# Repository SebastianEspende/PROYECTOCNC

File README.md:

# TALADRO CNC
### Introduccion

Este proyecto fue pensado y realizado con el fin de diseñar y construir un enrutador CNC de bajo costo, su 
principal función es agujerear placas PCB de producción caseras por estudiantes. Con este dispositivo se 
busca facilitar el proceso de la creación de proyectos que requieran placas electrónicas, permitiendo al 
usuario una mayor precisión y eficiencia en la perforación de placas, en comparación con los métodos 
manuales. Este proyecto también tiene como objetivo fomentar el aprendizaje practico de tecnologías CNC, 
de la electrónica y programación, con el fin de que sea una herramienta útil para los proyectos de electrónica 
y robótica.

#### Repositorio
- En el mismo se encuentran todos los recursos utilizados, como la parte electronica: donde se incluyen los diagramas y circuitos; los diseños 3D de las piezas utilizadas; y el codigo de programacion.
- No se incluyen las librerias, estas estaran al final de este archivo, algunas solo el nombre y otras en enlace a la pagina de donde provienen.

## Software

Se utiliza GRBL 1.1h, se incluye su link en el apartado de librerias

El codigo del ESP32 esta incluido por completo en este repositorio

## Para el futuro
A aquellos que les toque continuar nuestro proyecto, nos gustaria saberlo, les dejamos nuestros mails para que puedan contarnos, o si tienen alguna pregunta:
- espendesebastian@gmail.com
- josemcoronado671@gmail.com

### Palabras de precaución
los pines no son aleatorios, es importante que si quieren cambiarlo tengan en cuenta los grupos o puertos de los pines de un Arduino, si entran al cpu_map de GRBL se daran cuenta de lineas como esta para los 
pines que tienen algo en común como step de cada motor, dir de cada motor, limit switches, etc; 

```javascript
#define STEP_DDR        DDRD
#define STEP_PORT       PORTD
```
DDRD y PORTD no son solo nombres, se refieren al grupo de pines utiliado por los STEP en este caso, otro ejemplo
```javascript
#define DIRECTION_DDR     DDRD
#define DIRECTION_PORT    PORTD
```
Ambos utilizan el grupo D, que son del pin 0 al 7.
Grupo B utiliza pin 8 al 13.
es por eso que la declaracion de pines pareciera incorrecta, ejemplo 
#define X_LIMIT_BIT      1
Que utiliza el pin 9 pero se declara como 1, esto se debe a que utiliza el grupo B.

Para que la comunicacion entre el ESP32 y el Arduino funcione, tienen que tener el mismo GND, o al menos, conectarlos

### Librerias

- https://lcdmenu.forntoh.dev/overview/getting-started.html#installation
- https://github.com/gnea/grbl/releases/tag/v1.1h.20190825

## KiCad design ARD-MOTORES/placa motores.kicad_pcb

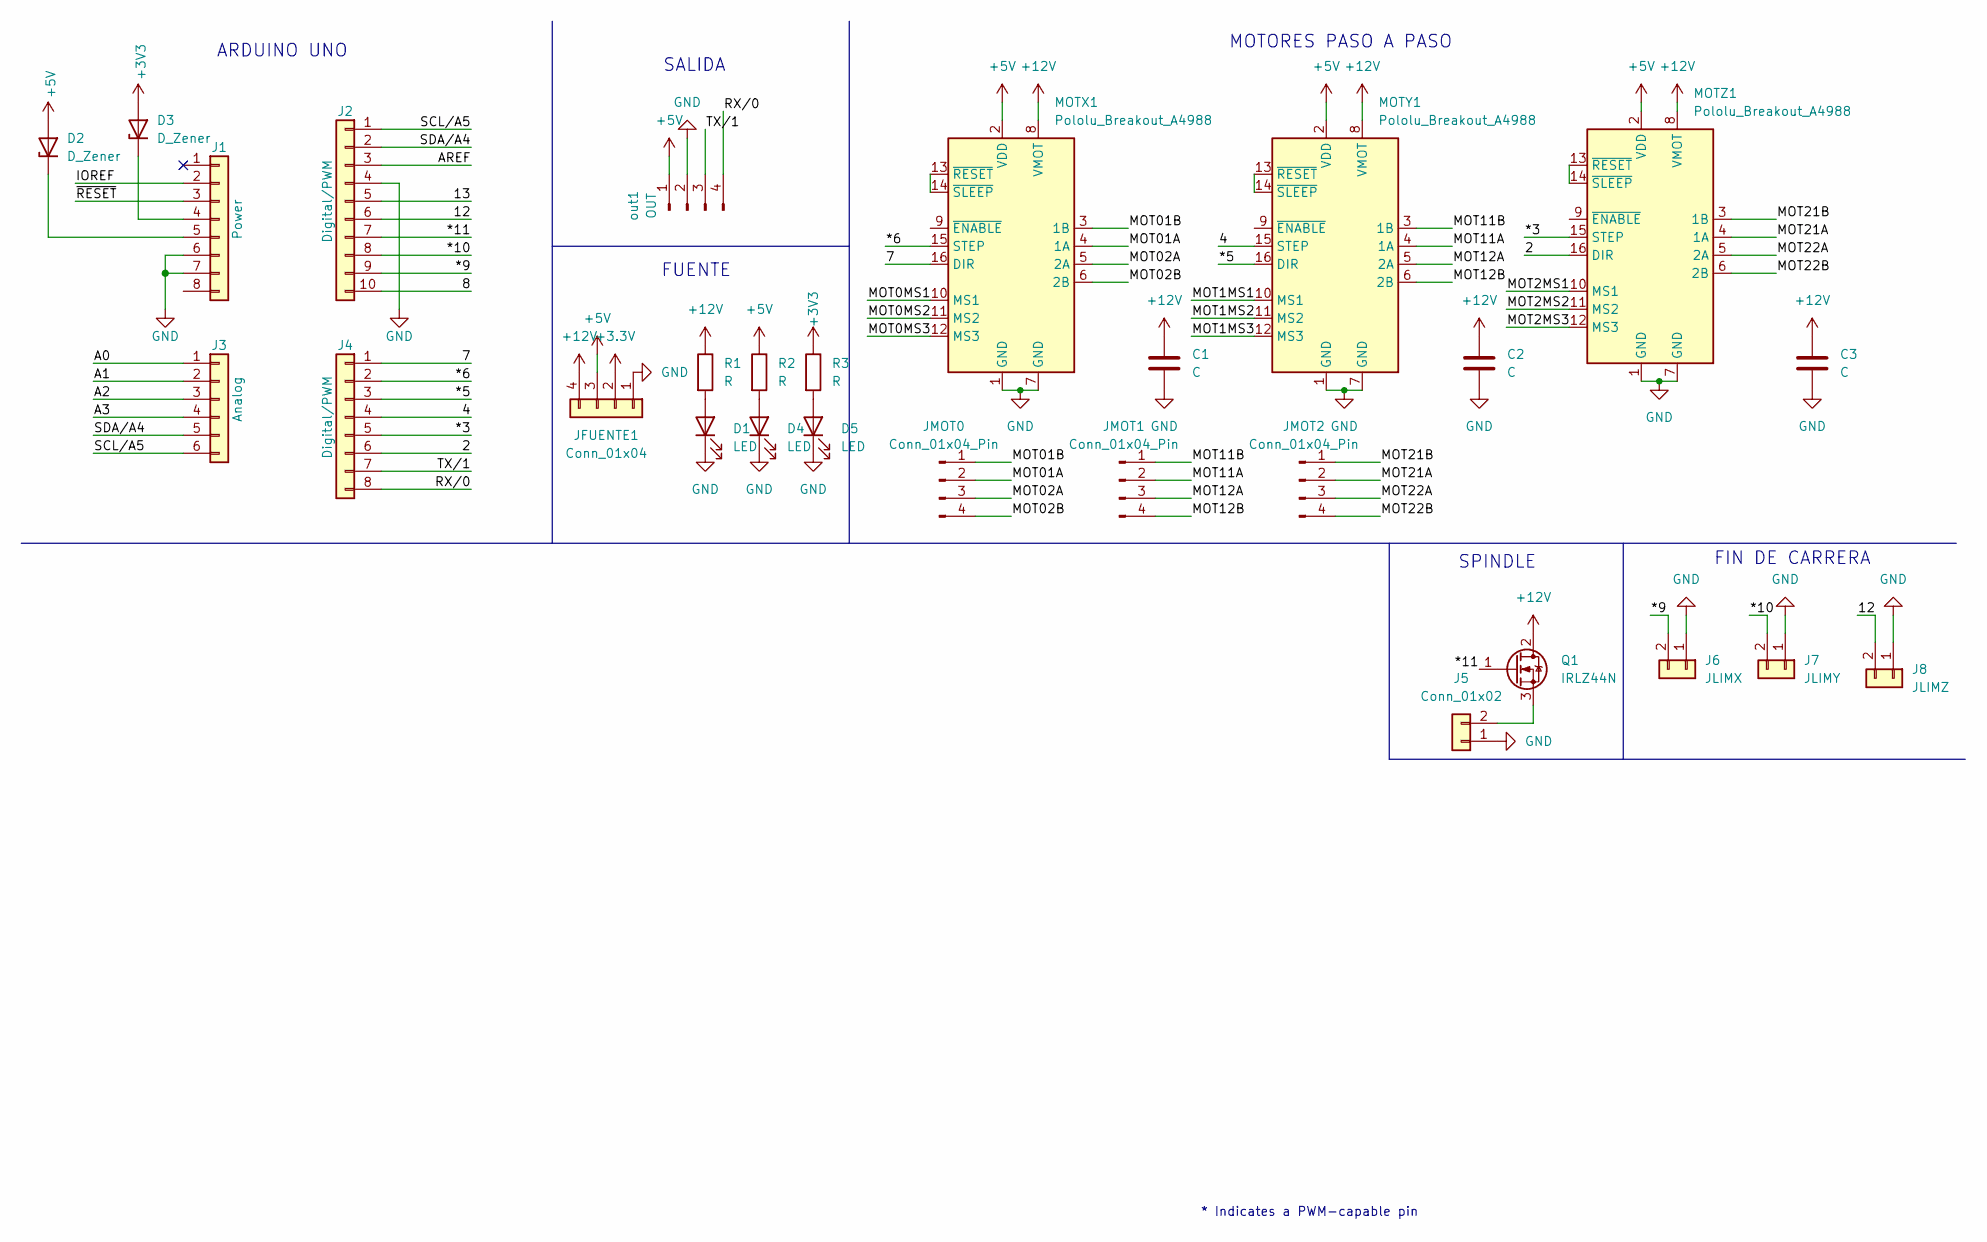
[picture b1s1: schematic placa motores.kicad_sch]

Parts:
C1, C2, C3: C; CP_Radial_D6.3mm_P2.50mm
D1, D4, D5: LED; LED_D5.0mm
D2, D3: D_Zener; D_DO-15_P12.70mm_Horizontal
J1: Power; PinSocket_1x08_P2.54mm_Vertical
J2: Digital/PWM; PinSocket_1x10_P2.54mm_Vertical
J3: Analog; PinSocket_1x06_P2.54mm_Vertical
J4: Digital/PWM; PinSocket_1x08_P2.54mm_Vertical
J5: Conn_01x02; PinHeader_1x02_P2.54mm_Vertical
J6: JLIMX; PinHeader_1x02_P2.54mm_Vertical
J7: JLIMY; PinHeader_1x02_P2.54mm_Vertical
J8: JLIMZ; PinHeader_1x02_P2.54mm_Vertical
JFUENTE1: Conn_01x04; TerminalBlock_Phoenix_MKDS-1,5-4_1x04_P5.00mm_Horizontal
JMOT0, JMOT1, JMOT2: Conn_01x04_Pin; PinHeader_1x04_P2.54mm_Vertical
MOTX1: Pololu_Breakout_A4988; Pololu_Breakout-16_15.2x20.3mm
MOTY1: Pololu_Breakout_A4988; Pololu_Breakout-16_15.2x20.3mm
MOTZ1: Pololu_Breakout_A4988; Pololu_Breakout-16_15.2x20.3mm
Q1: IRLZ44N; TO-220-3_Vertical
R1, R2, R3: R; R_Axial_DIN0414_L11.9mm_D4.5mm_P15.24mm_Horizontal
out1: OUT; PinHeader_1x04_P2.54mm_Vertical

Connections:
+5V: D2.2 (A), JFUENTE1.3, MOTX1.2 (VDD), MOTY1.2 (VDD), MOTZ1.2 (VDD), R2.1, out1.1
+12V: C1.1, C2.1, C3.1, JFUENTE1.4, MOTX1.8 (VMOT), MOTY1.8 (VMOT), MOTZ1.8 (VMOT), Q1.2 (D), R1.1
/2: J4.6, MOTZ1.16 (DIR)
/4: J4.4, MOTY1.15 (STEP)
/7: J4.1, MOTX1.16 (DIR)
/8: J2.10
/12: J2.6, J8.2
/13: J2.5
/*3: J4.5, MOTZ1.15 (STEP)
/*5: J4.3, MOTY1.16 (DIR)
/*6: J4.2, MOTX1.15 (STEP)
/*9: J2.9, J6.2
/*10: J2.8, J7.2
/*11: J2.7, Q1.1 (G)
/A0: J3.1
/A1: J3.2
/A2: J3.3
/A3: J3.4
/AREF: J2.3
/IOREF: J1.2
/MOT0MS1: MOTX1.10 (MS1)
/MOT0MS2: MOTX1.11 (MS2)
/MOT0MS3: MOTX1.12 (MS3)
/MOT01A: JMOT0.2, MOTX1.4 (1A)
/MOT01B: JMOT0.1, MOTX1.3 (1B)
/MOT1MS1: MOTY1.10 (MS1)
/MOT1MS2: MOTY1.11 (MS2)
/MOT1MS3: MOTY1.12 (MS3)
/MOT02A: JMOT0.3, MOTX1.5 (2A)
/MOT02B: JMOT0.4, MOTX1.6 (2B)
/MOT2MS1: MOTZ1.10 (MS1)
/MOT2MS2: MOTZ1.11 (MS2)
/MOT2MS3: MOTZ1.12 (MS3)
/MOT11A: JMOT1.2, MOTY1.4 (1A)
/MOT11B: JMOT1.1, MOTY1.3 (1B)
/MOT12A: JMOT1.3, MOTY1.5 (2A)
/MOT12B: JMOT1.4, MOTY1.6 (2B)
/MOT21A: JMOT2.2, MOTZ1.4 (1A)
/MOT21B: JMOT2.1, MOTZ1.3 (1B)
/MOT22A: JMOT2.3, MOTZ1.5 (2A)
/MOT22B: JMOT2.4, MOTZ1.6 (2B)
/RX/0: J4.8, out1.4
/SCL/A5: J2.1, J3.6
/SDA/A4: J2.2, J3.5
/TX/1: J4.7, out1.3
/~RESET: J1.3
GND: C1.2, C2.2, C3.2, D1.1 (K), D4.1 (K), D5.1 (K), J1.6, J1.7, J2.4, J5.1, J6.1, J7.1, J8.1, JFUENTE1.1, MOTX1.1 (GND), MOTX1.7 (GND), MOTY1.1 (GND), MOTY1.7 (GND), MOTZ1.1 (GND), MOTZ1.7 (GND), out1.2
unnamed: D1.2 (A), R1.2
unnamed: D2.1 (K), J1.5
unnamed: D3.1 (K), J1.4
unnamed: D4.2 (A), R2.2
unnamed: D5.2 (A), R3.2
unnamed: J5.2, Q1.3 (S)
unnamed: MOTX1.13 (~RESET), MOTX1.14 (~SLEEP)
unnamed: MOTY1.13 (~RESET), MOTY1.14 (~SLEEP)
unnamed: MOTZ1.13 (~RESET), MOTZ1.14 (~SLEEP)

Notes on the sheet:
ARDUINO UNO
FUENTE
MOTORES PASO A PASO
* Indicates a PWM-capable pin
SALIDA
SPINDLE
FIN DE CARRERA

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
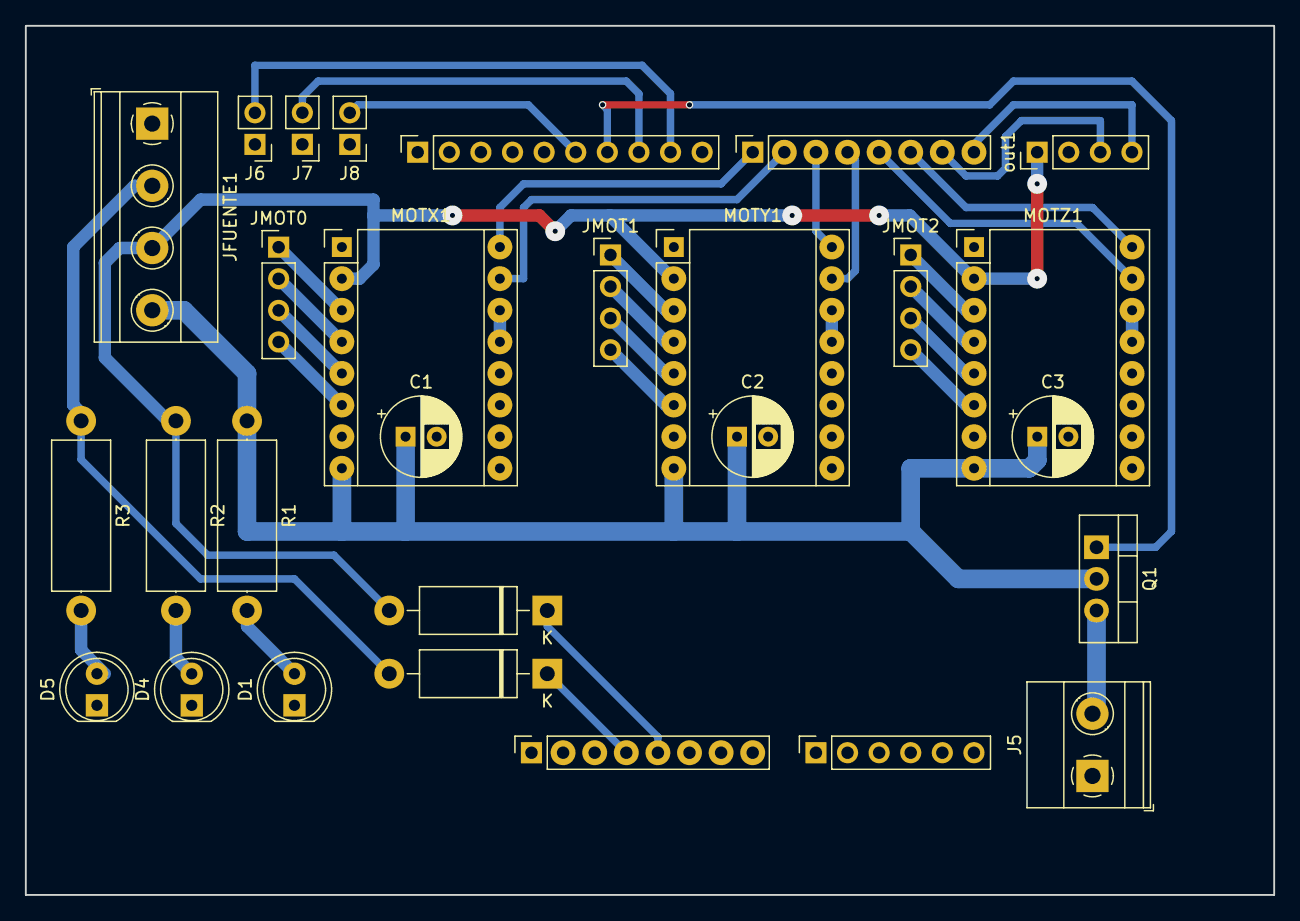
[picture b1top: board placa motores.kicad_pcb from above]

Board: 2 copper layers, 100.3 x 69.8 mm, 28 parts (0 on the bottom side), 39 nets.

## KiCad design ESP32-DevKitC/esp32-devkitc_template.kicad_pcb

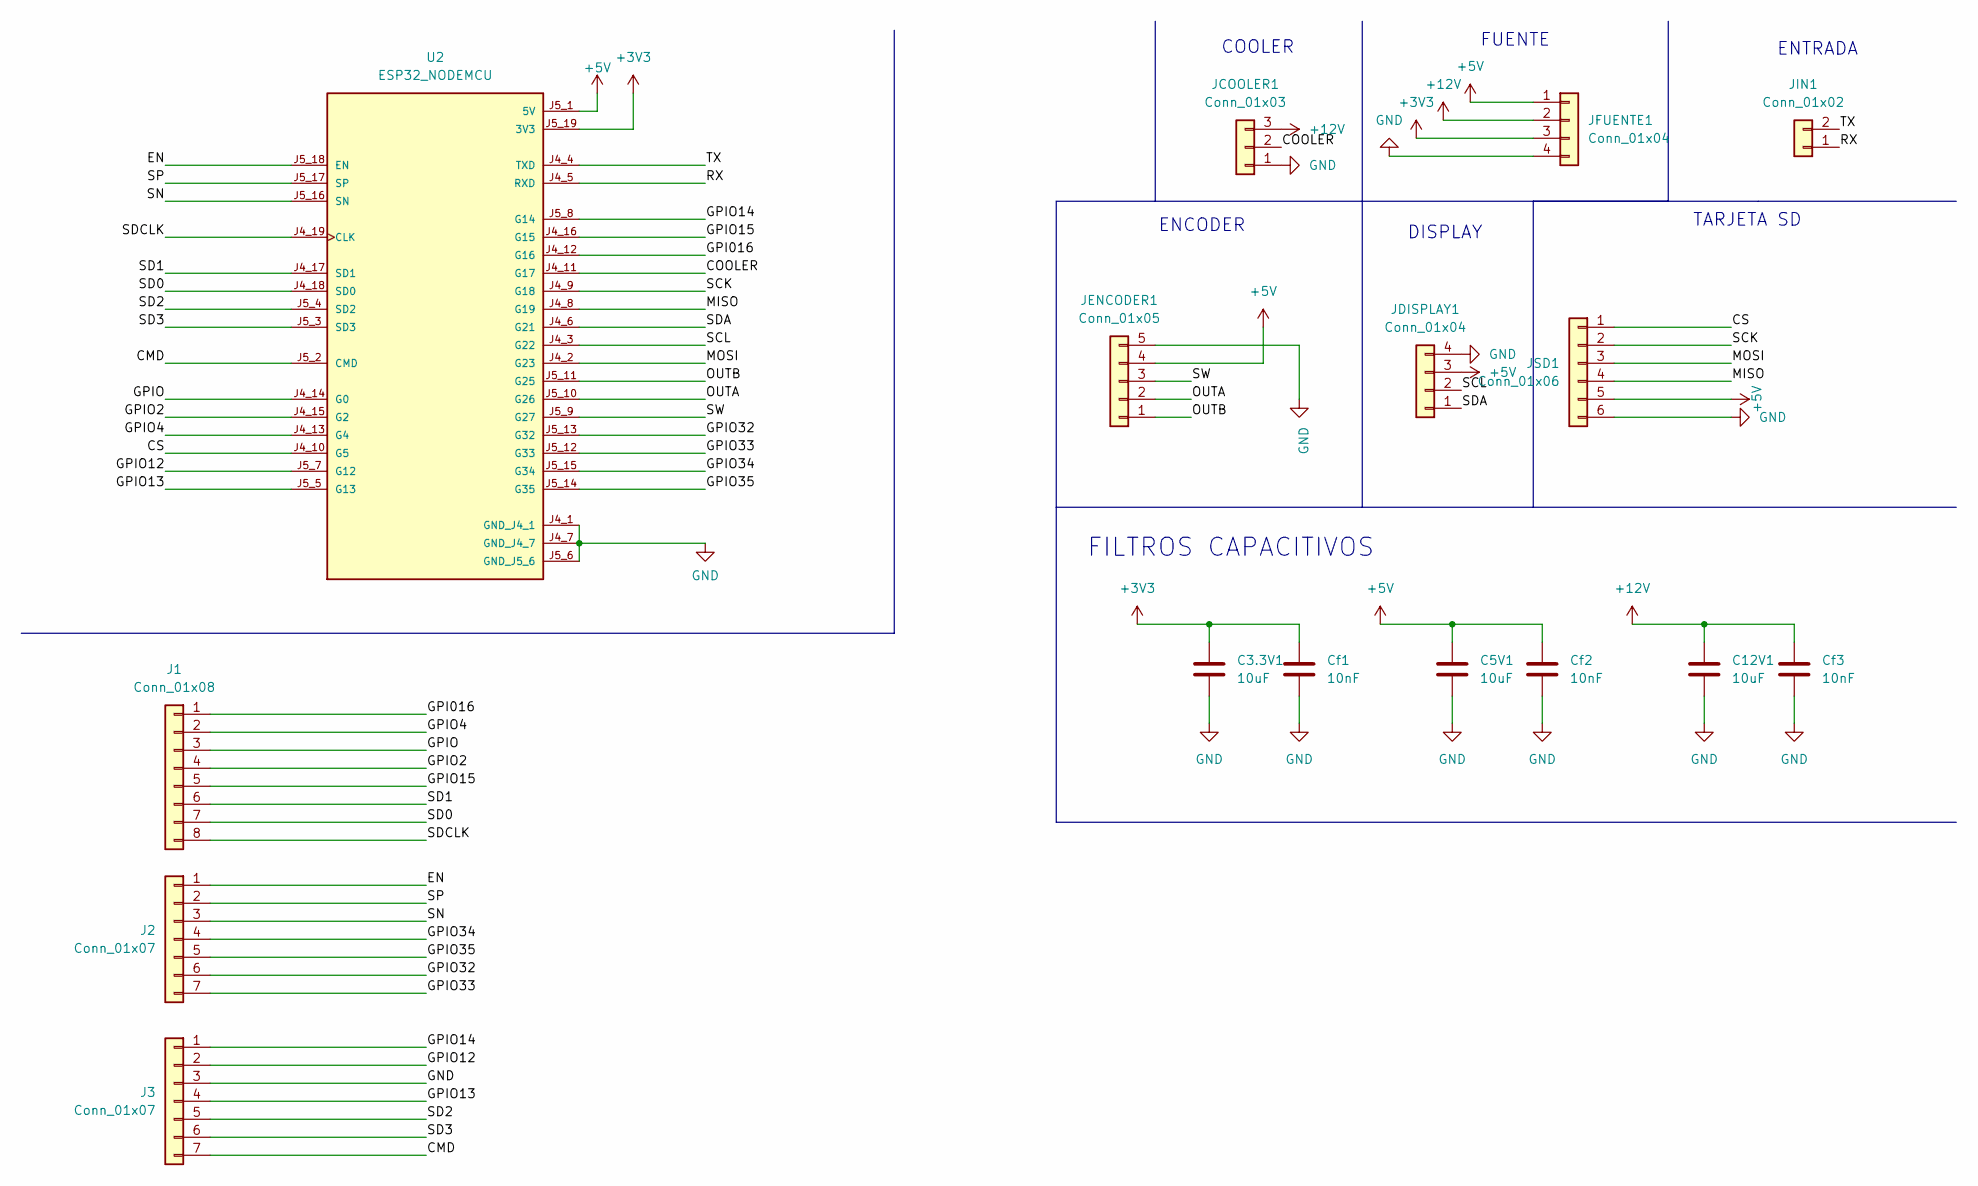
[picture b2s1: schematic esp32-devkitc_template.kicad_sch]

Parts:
C3.3V1, C5V1, C12V1: 10uF; CP_Radial_D5.0mm_P2.50mm
Cf1, Cf2, Cf3: 10nF; C_Disc_D6.0mm_W2.5mm_P5.00mm
J1: Conn_01x08; PinHeader_1x08_P2.54mm_Vertical
J2, J3: Conn_01x07; PinHeader_1x07_P2.54mm_Vertical
JCOOLER1: Conn_01x03; PinHeader_1x03_P2.54mm_Vertical
JDISPLAY1: Conn_01x04; PinSocket_1x04_P2.54mm_Vertical
JENCODER1: Conn_01x05; PinSocket_1x05_P2.54mm_Vertical
JFUENTE1: Conn_01x04; TerminalBlock_Phoenix_MKDS-1,5-4_1x04_P5.00mm_Horizontal
JIN1: Conn_01x02; PinHeader_1x02_P2.54mm_Vertical
JSD1: Conn_01x06; PinHeader_1x06_P2.54mm_Vertical
U2: ESP32_NODEMCU; MODULE_ESP32_NODEMCU

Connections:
+3V3: C3.3V1.1, Cf1.1, JFUENTE1.3, U2.J5_19 (3V3)
+5V: C5V1.1, Cf2.1, JDISPLAY1.3, JENCODER1.4, JFUENTE1.1, JSD1.5, U2.J5_1 (5V)
+12V: C12V1.1, Cf3.1, JCOOLER1.3, JFUENTE1.2
/CMD: J3.7, U2.J5_2 (CMD)
/COOLER: JCOOLER1.2, U2.J4_11 (G17)
/CS: JSD1.1, U2.J4_10 (G5)
/EN: J2.1, U2.J5_18 (EN)
/GPI016: J1.1, U2.J4_12 (G16)
/GPIO: J1.3, U2.J4_14 (G0)
/GPIO2: J1.4, U2.J4_15 (G2)
/GPIO4: J1.2, U2.J4_13 (G4)
/GPIO12: J3.2, U2.J5_7 (G12)
/GPIO13: J3.4, U2.J5_5 (G13)
/GPIO14: J3.1, U2.J5_8 (G14)
/GPIO15: J1.5, U2.J4_16 (G15)
/GPIO32: J2.6, U2.J5_13 (G32)
/GPIO33: J2.7, U2.J5_12 (G33)
/GPIO34: J2.4, U2.J5_15 (G34)
/GPIO35: J2.5, U2.J5_14 (G35)
/MISO: JSD1.4, U2.J4_8 (G19)
/MOSI: JSD1.3, U2.J4_2 (G23)
/OUTA: JENCODER1.2, U2.J5_10 (G26)
/OUTB: JENCODER1.1, U2.J5_11 (G25)
/RX: JIN1.1, U2.J4_5 (RXD)
/SCK: JSD1.2, U2.J4_9 (G18)
/SCL: JDISPLAY1.2, U2.J4_3 (G22)
/SD0: J1.7, U2.J4_18 (SD0)
/SD1: J1.6, U2.J4_17 (SD1)
/SD2: J3.5, U2.J5_4 (SD2)
/SD3: J3.6, U2.J5_3 (SD3)
/SDA: JDISPLAY1.1, U2.J4_6 (G21)
/SDCLK: J1.8, U2.J4_19 (CLK)
/SN: J2.3, U2.J5_16 (SN)
/SP: J2.2, U2.J5_17 (SP)
/SW: JENCODER1.3, U2.J5_9 (G27)
/TX: JIN1.2, U2.J4_4 (TXD)
GND: C3.3V1.2, C5V1.2, C12V1.2, Cf1.2, Cf2.2, Cf3.2, J3.3, JCOOLER1.1, JDISPLAY1.4, JENCODER1.5, JFUENTE1.4, JSD1.6, U2.J4_1 (GND_J4_1), U2.J4_7 (GND_J4_7), U2.J5_6 (GND_J5_6)

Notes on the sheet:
TARJETA SD
FUENTE
COOLER
FILTROS CAPACITIVOS
ENTRADA
ENCODER
DISPLAY

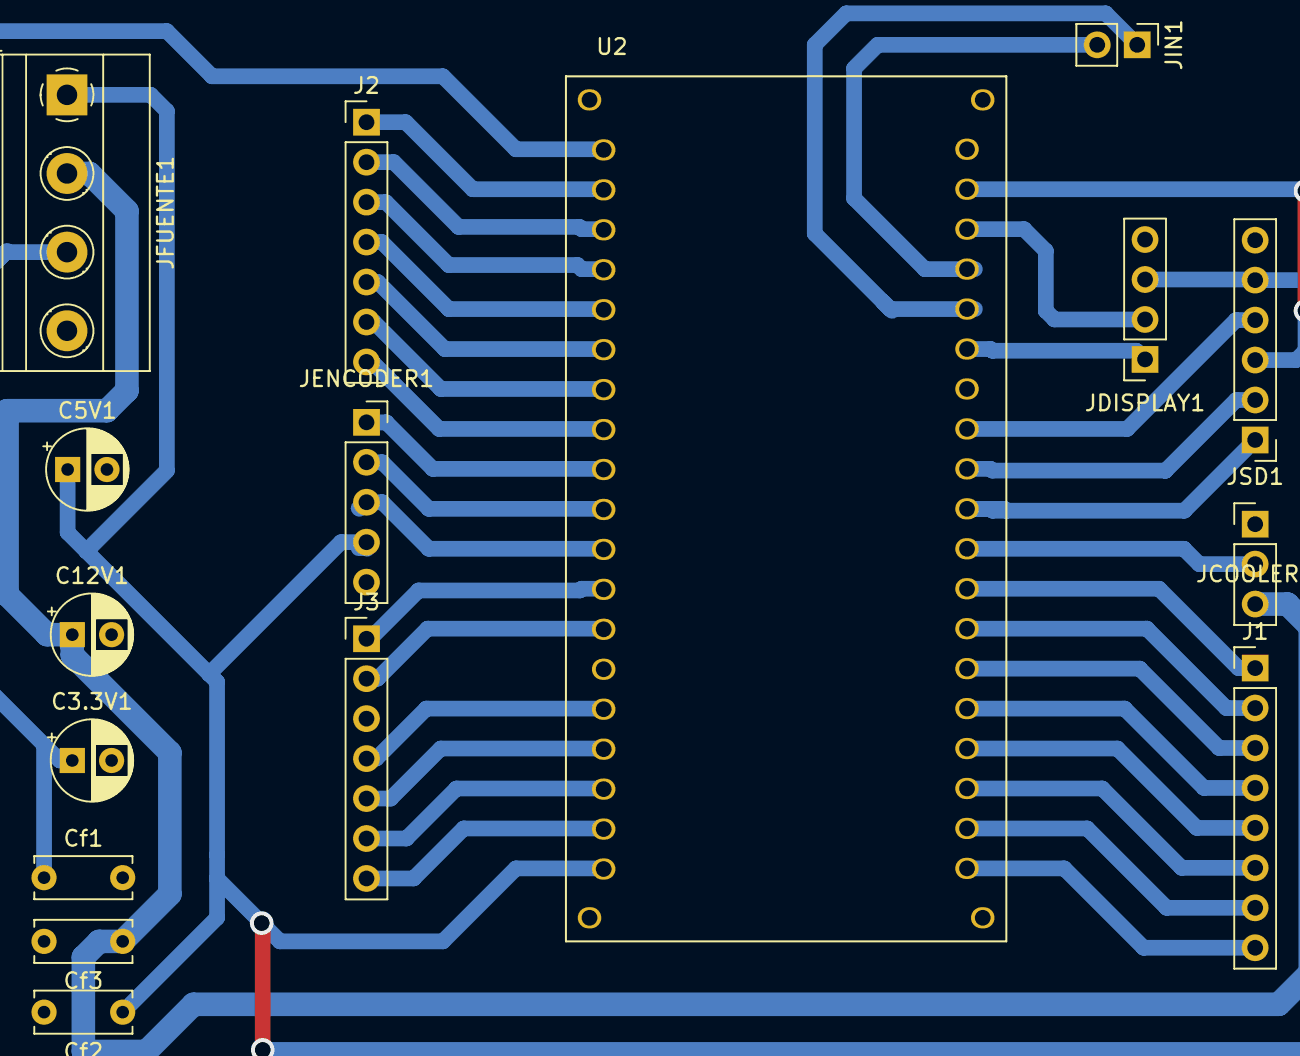
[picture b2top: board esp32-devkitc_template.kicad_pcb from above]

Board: 2 copper layers, 16 parts (0 on the bottom side), 37 nets.

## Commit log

2024-12-08 3d terminado
2024-12-08 placas
2024-12-09 cpu_map
2024-12-17 placa motores
2025-02-04 servidor completado y funcionando
2025-03-05 README.md
2025-03-05 Organizacion
2025-03-05 cpu_map y informe
